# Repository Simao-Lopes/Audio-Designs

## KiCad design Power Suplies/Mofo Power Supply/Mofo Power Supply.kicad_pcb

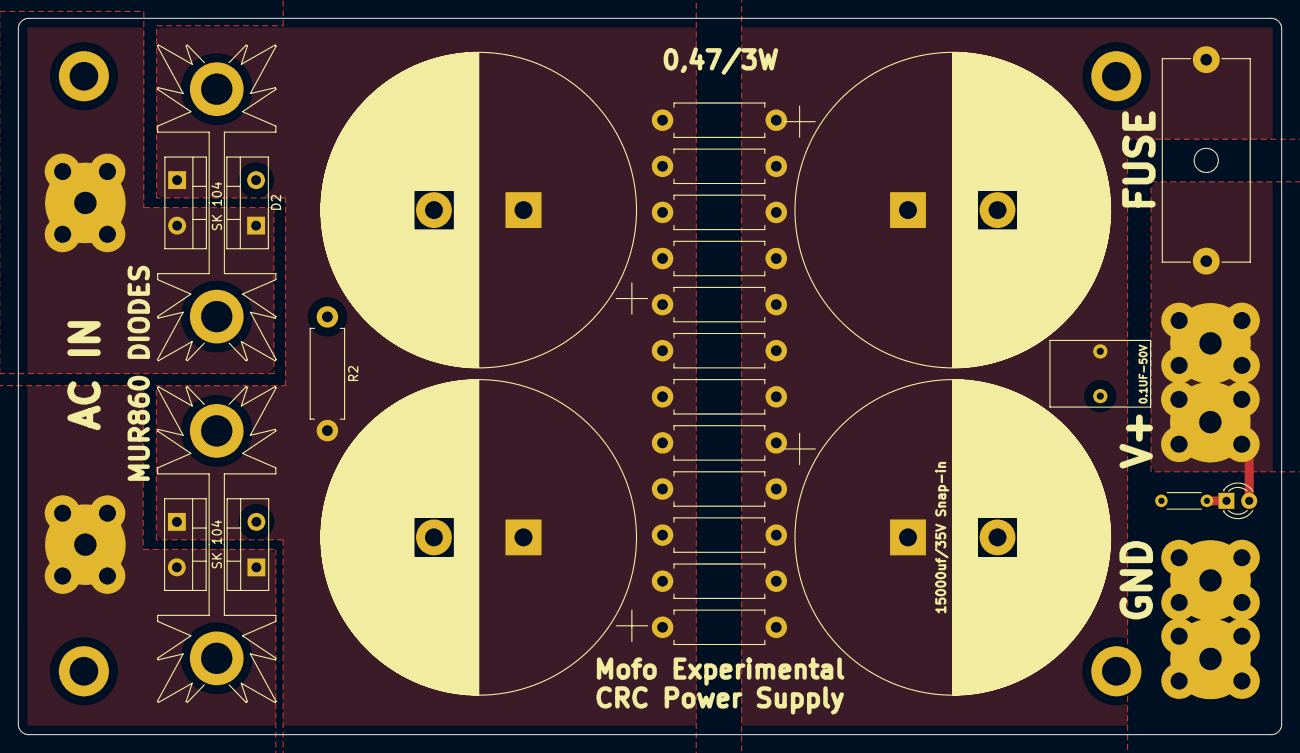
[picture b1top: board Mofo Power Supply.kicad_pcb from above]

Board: 2 copper layers, 141.1 x 80.0 mm, 35 parts (0 on the bottom side), 6 nets.

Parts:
0.1UF-50V: C; C_Rect_L7.2mm_W11.0mm_P5.00mm_FKS2_FKP2_MKS2_MKP2
AC1, AC2: Screw_Terminal_01x01; M4_Screw_Terminal
C1, C2, C3, C4: CP; CP_Radial_D35.0mm_P10.00mm_SnapIn
D1: LED; LED_D3.0mm
D2, D3, D4, D5: D; TO-220-2_Vertical
FUSE: Fuse; Fuseholder_Cylinder-5x20mm_Schurter_0031_8201_Horizontal_Op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
GND1, GND2: M4_Screw_Terminal
H1, H2, H3, H4: MountingHole; MountingHole_3.2mm_M3_DIN965_Pad
R2, R3, R3#2, R3#3, R4, R4#2, R4#3, R5, R5#2, R5#3: R; R_Axial_DIN0411_L9.9mm_D3.6mm_P12.70mm_Horizontal
R6, R6#2, R6#3: R7; R_Axial_DIN0411_L9.9mm_D3.6mm_P12.70mm_Horizontal
R11: R; R_Axial_DIN0204_L3.6mm_D1.6mm_P5.08mm_Horizontal
V1+1, V2+1: M4_Screw_Terminal

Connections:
/GND: 0.1UF-50V.2, C1.2, C2.2, C3.2, C4.2, D2.2 (A), D4.2 (A), GND1.1, GND2.1, R2.1, R11.1
/V+: 0.1UF-50V.1, C1.1, C2.1, C3.1, C4.1, D3.1 (K), D5.1 (K), FUSE.2, R2.2, R3.1, R3.2, R3#2.1, R3#2.2, R3#3.1, R3#3.2, R4.1, R4.2, R4#2.1, R4#2.2, R4#3.1, R4#3.2, R5.1, R5.2, R5#2.1, R5#2.2, R5#3.1, R5#3.2, R6.1, R6.2, R6#2.1, R6#2.2, R6#3.1, R6#3.2
unnamed: AC1.1, D4.1 (K), D5.2 (A)
unnamed: AC2.1, D2.1 (K), D3.2 (A)
unnamed: D1.1 (K), R11.2
unnamed: D1.2 (A), FUSE.1, V1+1.1, V2+1.1

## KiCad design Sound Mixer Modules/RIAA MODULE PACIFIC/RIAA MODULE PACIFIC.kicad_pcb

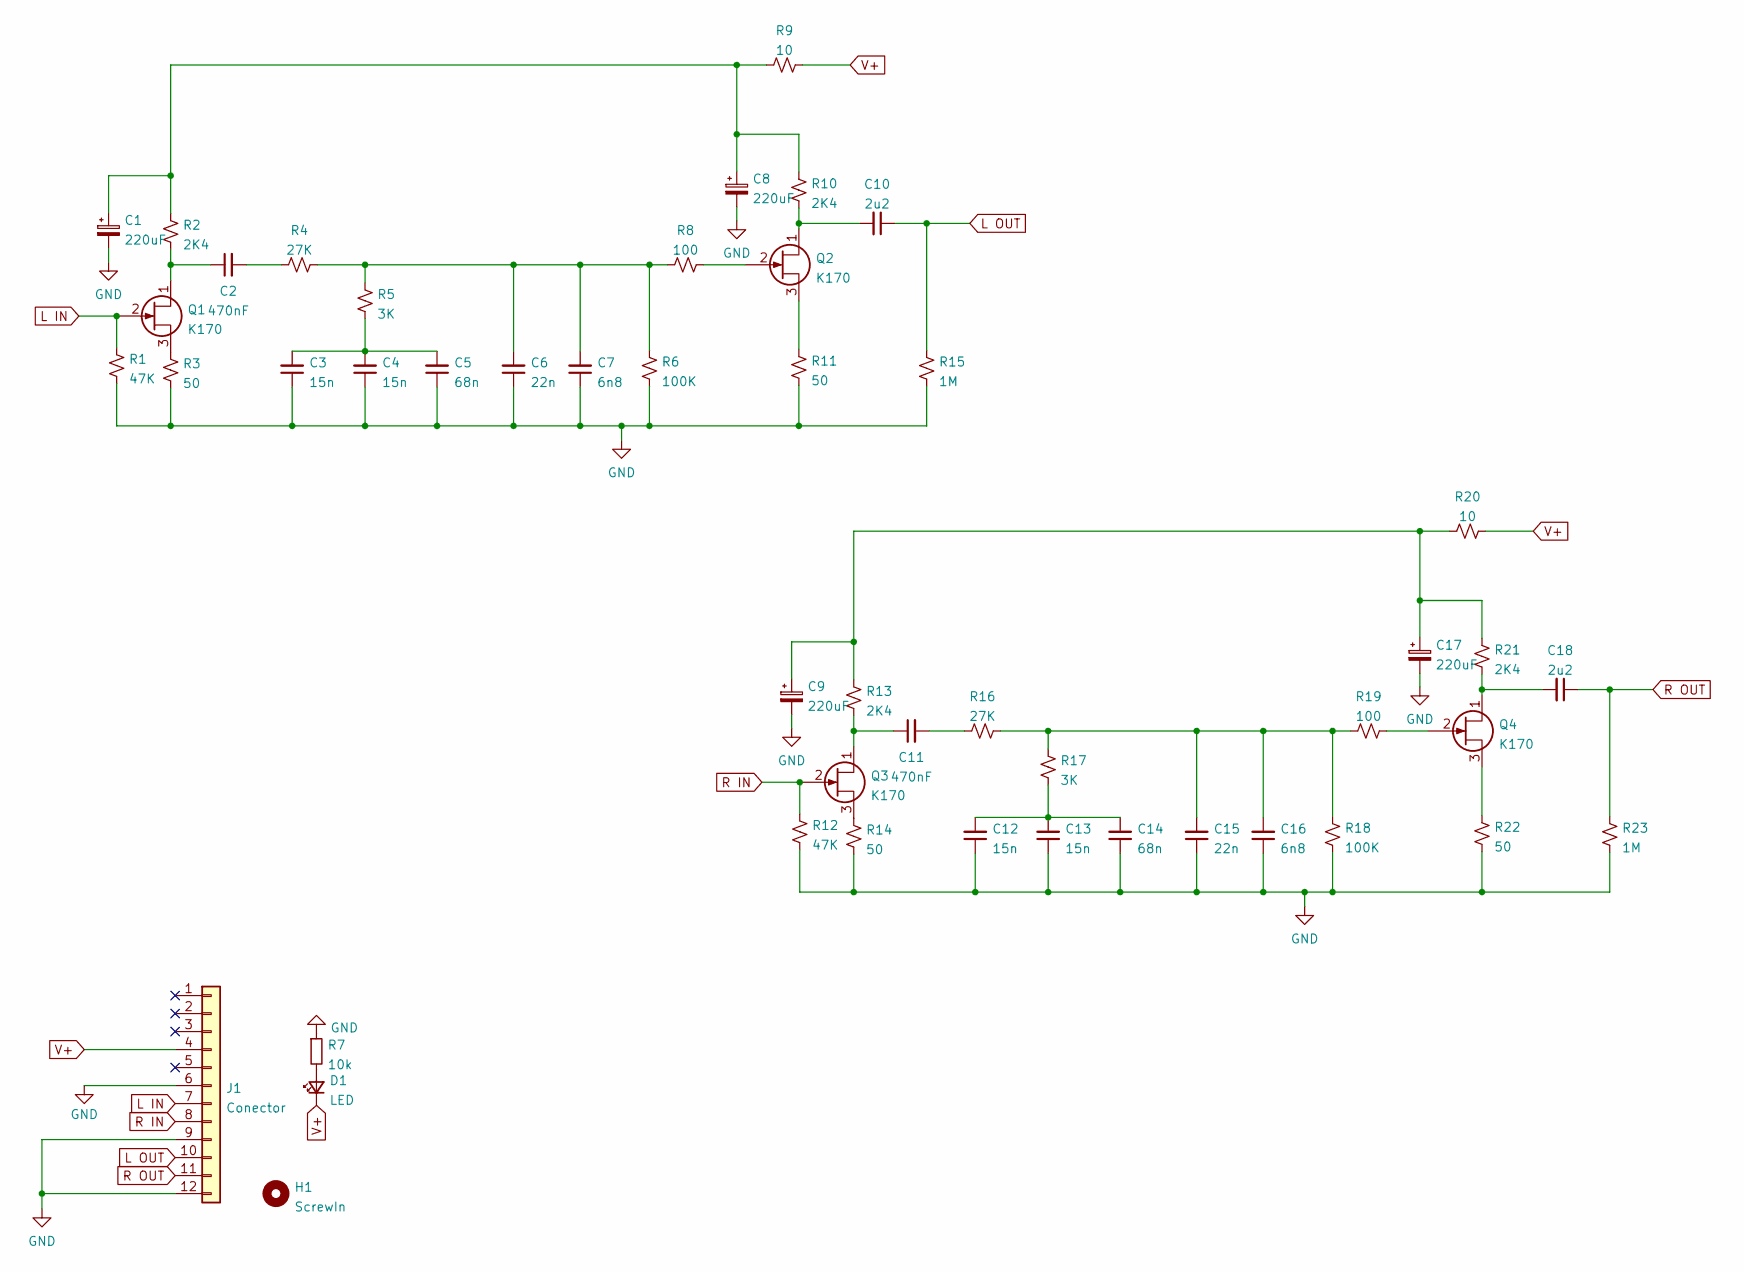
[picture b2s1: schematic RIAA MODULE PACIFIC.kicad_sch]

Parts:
C1, C8, C9, C17: 220uF; CP_Radial_D10.0mm_P5.00mm_P7.50mm
C2, C11: 470nF; C_Rect_L13.0mm_W8.0mm_P10.00mm_FKS3_FKP3_MKS4
C3, C4, C12, C13: 15n; C_Rect_L13.0mm_W8.0mm_P10.00mm_FKS3_FKP3_MKS4
C5, C14: 68n; C_Rect_L13.0mm_W8.0mm_P10.00mm_FKS3_FKP3_MKS4
C6, C15: 22n; C_Rect_L13.0mm_W8.0mm_P10.00mm_FKS3_FKP3_MKS4
C7, C16: 6n8; C_Rect_L13.0mm_W8.0mm_P10.00mm_FKS3_FKP3_MKS4
C10, C18: 2u2; C_Axial_L19.0mm_D8.0mm_P25.00mm_Horizontal
D1: LED; D_0201_0603Metric_Pad0.64x0.40mm_HandSolder
H1: ScrewIn; MountingHole_3.2mm_M3
J1: Conector; PinHeader_2x12_P2.54mm_Vertical
Q1, Q2, Q3, Q4: K170; TO-92
R1, R12: 47K; R_1206_3216Metric
R2, R10, R13, R21: 2K4; R_1206_3216Metric
R3, R11, R14, R22: 50; R_1206_3216Metric
R4, R16: 27K; R_1206_3216Metric
R5, R17: 3K; R_1206_3216Metric
R6, R18: 100K; R_1206_3216Metric
R7: 10k; R_1206_3216Metric
R8, R19: 100; R_1206_3216Metric
R9, R20: 10; R_1206_3216Metric
R15, R23: 1M; R_1206_3216Metric

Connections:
GND: C1.2, C3.1, C4.1, C5.1, C6.1, C7.1, C8.2, C9.2, C12.1, C13.1, C14.1, C15.1, C16.1, C17.2, J1.6, J1.9, J1.12, R1.2, R3.2, R6.1, R7.1, R11.2, R12.2, R14.2, R15.2, R18.1, R22.2, R23.2
L IN: J1.7, Q1.2 (G), R1.1
L OUT: C10.1, J1.10, R15.1
unnamed: C1.1, C8.1, R2.1, R9.1, R10.1
unnamed: C2.1, Q1.1 (D), R2.2
unnamed: C2.2, R4.1
unnamed: C3.2, C4.2, C5.2, R5.1
unnamed: C6.2, C7.2, R4.2, R5.2, R6.2, R8.2
unnamed: C10.2, Q2.1 (D), R10.2
unnamed: C11.1, Q3.1 (D), R13.2
unnamed: C11.2, R16.1
unnamed: C12.2, C13.2, C14.2, R17.1
unnamed: C15.2, C16.2, R16.2, R17.2, R18.2, R19.2
unnamed: C9.1, C17.1, R13.1, R20.1, R21.1
unnamed: C18.2, Q4.1 (D), R21.2
unnamed: D1.2 (A), R7.2
unnamed: Q1.3 (S), R3.1
unnamed: Q2.2 (G), R8.1
unnamed: Q2.3 (S), R11.1
unnamed: Q3.3 (S), R14.1
unnamed: Q4.2 (G), R19.1
unnamed: Q4.3 (S), R22.1
R IN: J1.8, Q3.2 (G), R12.1
R OUT: C18.1, J1.11, R23.1
V+: D1.1 (K), J1.4, R9.2, R20.2

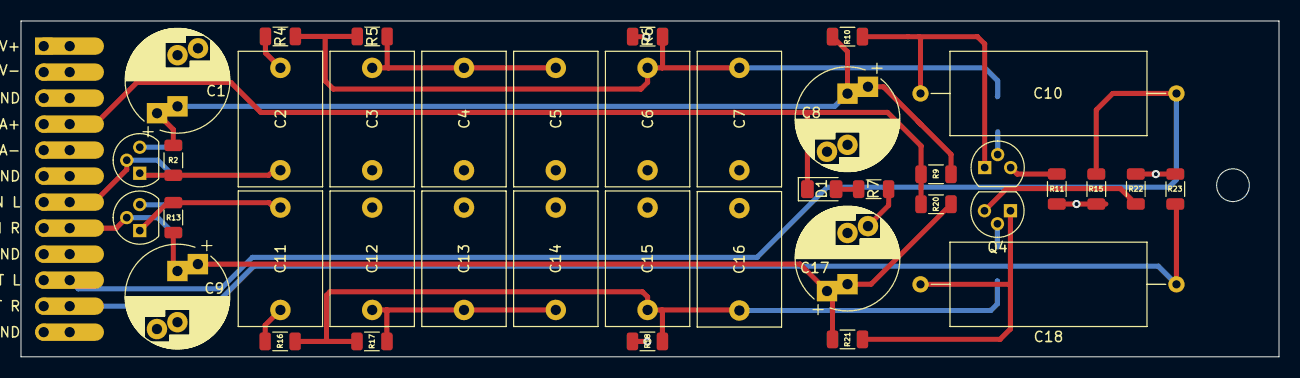
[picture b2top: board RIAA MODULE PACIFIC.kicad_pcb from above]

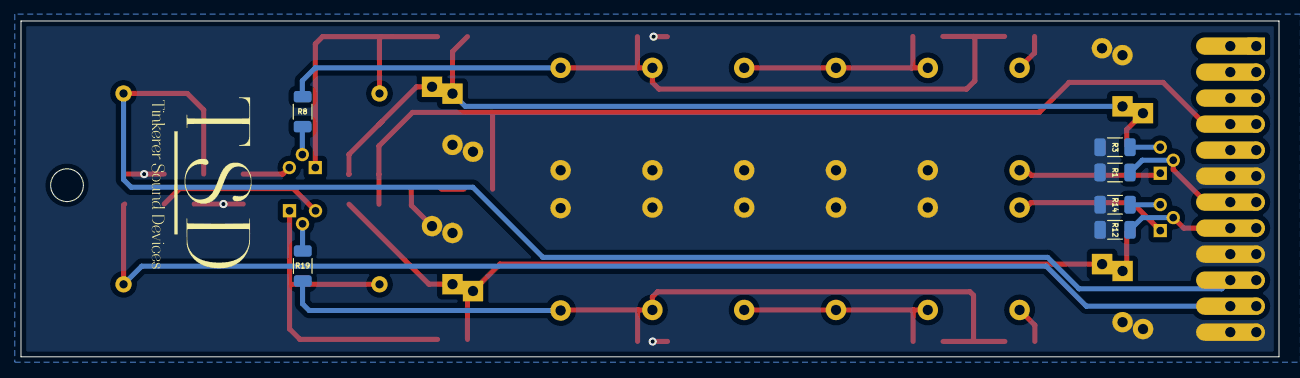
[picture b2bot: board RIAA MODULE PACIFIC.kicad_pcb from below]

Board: 2 copper layers, 122.9 x 32.8 mm, 48 parts (6 on the bottom side), 25 nets.

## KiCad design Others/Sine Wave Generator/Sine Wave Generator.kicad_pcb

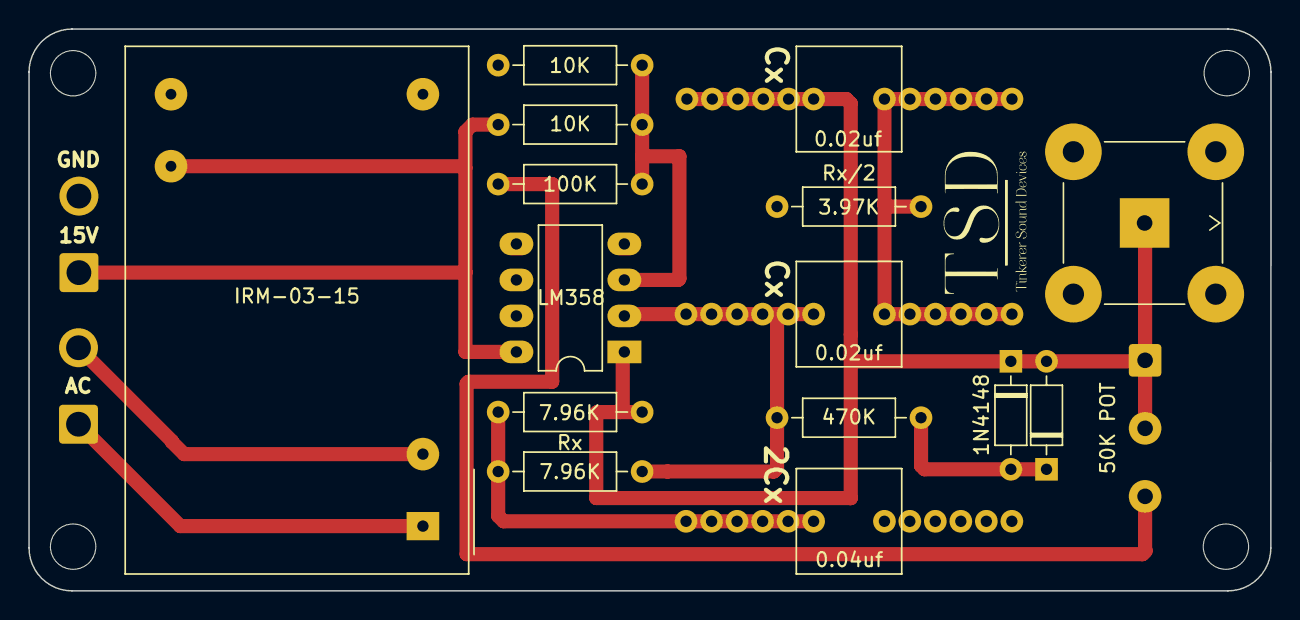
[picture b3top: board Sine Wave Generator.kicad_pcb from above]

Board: 2 copper layers, 87.6 x 39.7 mm, 21 parts (0 on the bottom side), 11 nets.

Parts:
1, 2, 3: (no value)
15V: AC; SolderWire-1sqmm_1x02_P5.4mm_D1.4mm_OD2.7mm
50K POT: 50K; SolderWire-0.5sqmm_1x03_P4.8mm_D0.9mm_OD2.3mm
AC: AC; SolderWire-1sqmm_1x02_P5.4mm_D1.4mm_OD2.7mm
C3, C5: 0.02uf; C_Rect_L7.2mm_W7.2mm_P5.00mm_FKS2_FKP2_MKS2_MKP2
C4: 0.04uf; C_Rect_L7.2mm_W7.2mm_P5.00mm_FKS2_FKP2_MKS2_MKP2
D1, D2: 1N4148; D_DO-35_SOD27_P7.62mm_Horizontal
J3: Conn_Coaxial; BNC_TEConnectivity_1478035_Horizontal
PS1: IRM-03-15; Converter_ACDC_MeanWell_IRM-03-xx_THT
R1, R2: 10K; R_Axial_DIN0207_L6.3mm_D2.5mm_P10.16mm_Horizontal
R4: 100K; R_Axial_DIN0207_L6.3mm_D2.5mm_P10.16mm_Horizontal
R5: 470K; R_Axial_DIN0207_L6.3mm_D2.5mm_P10.16mm_Horizontal
R7: 7.96K; R_Axial_DIN0207_L6.3mm_D2.5mm_P10.16mm_Horizontal
Rx: 7.96K; R_Axial_DIN0207_L6.3mm_D2.5mm_P10.16mm_Horizontal
Rx/2: 3.97K; R_Axial_DIN0207_L6.3mm_D2.5mm_P10.16mm_Horizontal
U1: LM358; DIP-8_W7.62mm_LongPads

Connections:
GND: 15V.2, C4.1, J3.2 (Ext), PS1.14 (-Vo), R2.2, Rx/2.1, U1.4 (V-)
unnamed: C3.1, R5.1, Rx.1, U1.2 (-)
unnamed: C3.2, C5.1, Rx/2.2
unnamed: C4.2, R7.1, Rx.2
unnamed: 1.2, 2.2, 3.2, 50K POT.1, 50K POT.2, C5.2, D1.1 (K), D2.2 (A), J3.1 (In), R7.2, U1.1
unnamed: D1.2 (A), D2.1 (K), R5.2
unnamed: AC.1, PS1.1 (AC/L)
unnamed: AC.2, PS1.3 (AC/N)
unnamed: 15V.1, PS1.16 (+Vo), R1.1, U1.8 (V+)
unnamed: R1.2, R2.1, R4.1, U1.3 (+)
unnamed: 50K POT.3, R4.2

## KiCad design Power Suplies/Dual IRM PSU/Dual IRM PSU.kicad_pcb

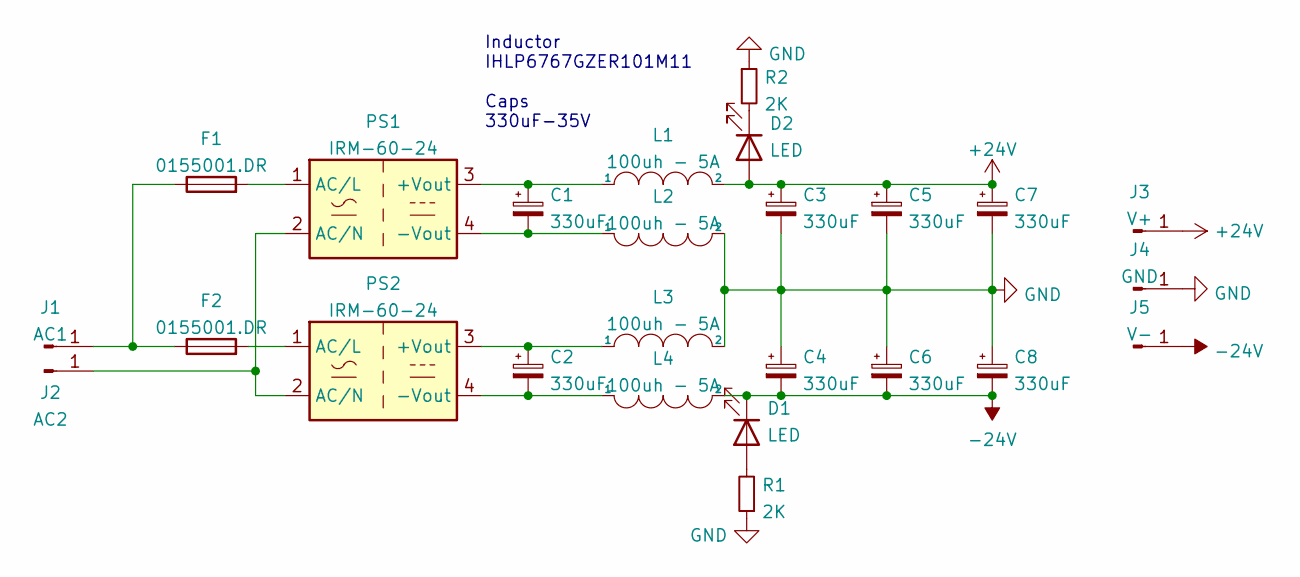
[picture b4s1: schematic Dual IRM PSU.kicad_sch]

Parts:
C1, C2, C3, C4, C5, C6, C7, C8: 330uF; CP_Elec_16x17.5
D1, D2: LED; LED_1210_3225Metric
F1, F2: 0155001.DR; Fuseholder_Littelfuse_100_series_5x20mm
J1: AC1; Spade Conector 6.3mm TE_1217861
J2: AC2; Spade Conector 6.3mm TE_1217861
J3: V+; Spade Conector 6.3mm TE_1217861
J4: GND; Spade Conector 6.3mm TE_1217861
J5: V-; Spade Conector 6.3mm TE_1217861
L1, L2, L3, L4: 100uh - 5A; L_Vishay_IHLP-6767
PS1, PS2: IRM-60-24; Converter_ACDC_MeanWell_IRM-60-xx_THT
R1, R2: 2K; R_1210_3225Metric

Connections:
+24V: C3.1, C5.1, C7.1, D2.2 (A), J3.1, L1.2
-24V: C4.2, C6.2, C8.2, D1.1 (K), J5.1, L4.2
GND: C3.2, C4.1, C5.2, C6.1, C7.2, C8.1, J4.1, L2.2, L3.2, R1.1, R2.1
unnamed: C1.1, L1.1, PS1.3 (+Vout)
unnamed: C1.2, L2.1, PS1.4 (-Vout)
unnamed: C2.1, L3.1, PS2.3 (+Vout)
unnamed: C2.2, L4.1, PS2.4 (-Vout)
unnamed: D1.2 (A), R1.2
unnamed: D2.1 (K), R2.2
unnamed: F1.1, F2.1, J1.1
unnamed: F1.2, PS1.1 (AC/L)
unnamed: F2.2, PS2.1 (AC/L)
unnamed: J2.1, PS1.2 (AC/N), PS2.2 (AC/N)

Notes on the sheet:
Inductor IHLP6767GZER101M11 Caps 330uF-35V

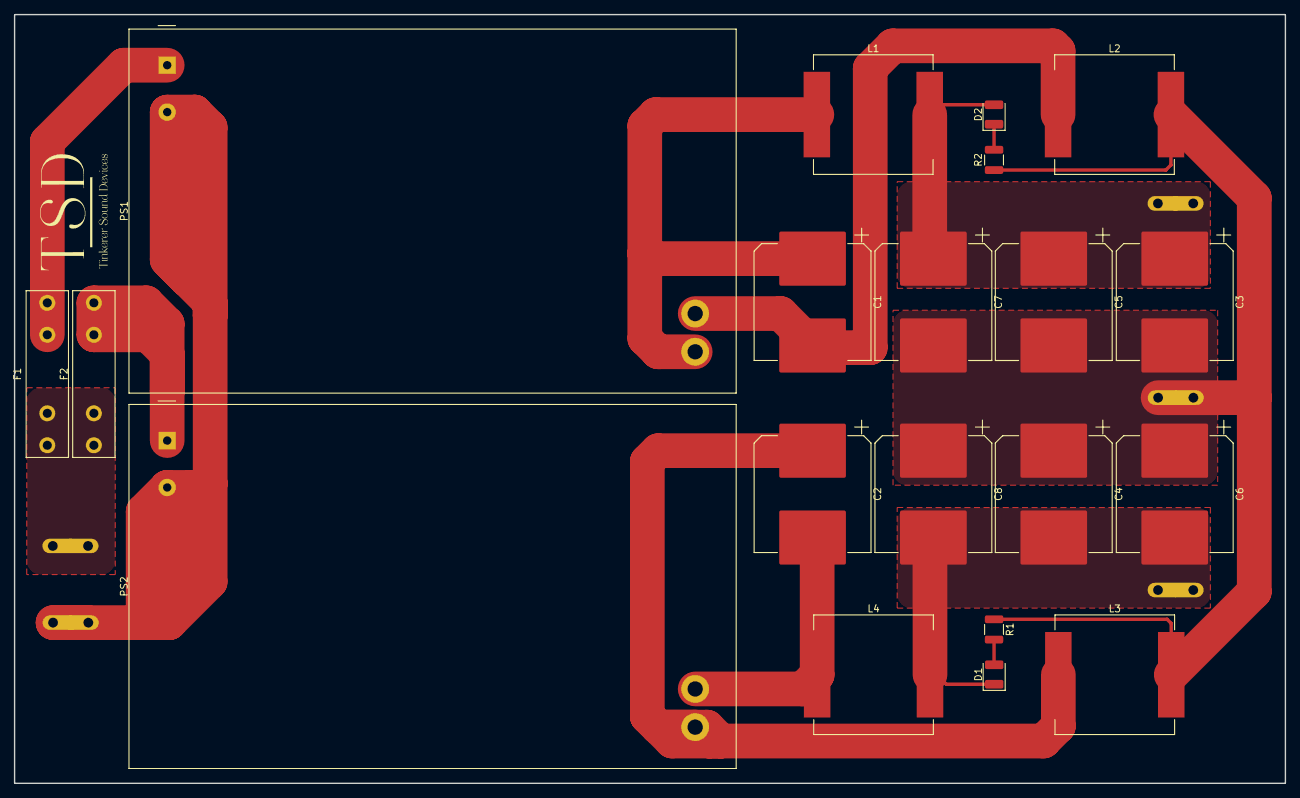
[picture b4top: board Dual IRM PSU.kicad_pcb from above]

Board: 2 copper layers, 182.9 x 110.7 mm, 25 parts (0 on the bottom side), 13 nets.

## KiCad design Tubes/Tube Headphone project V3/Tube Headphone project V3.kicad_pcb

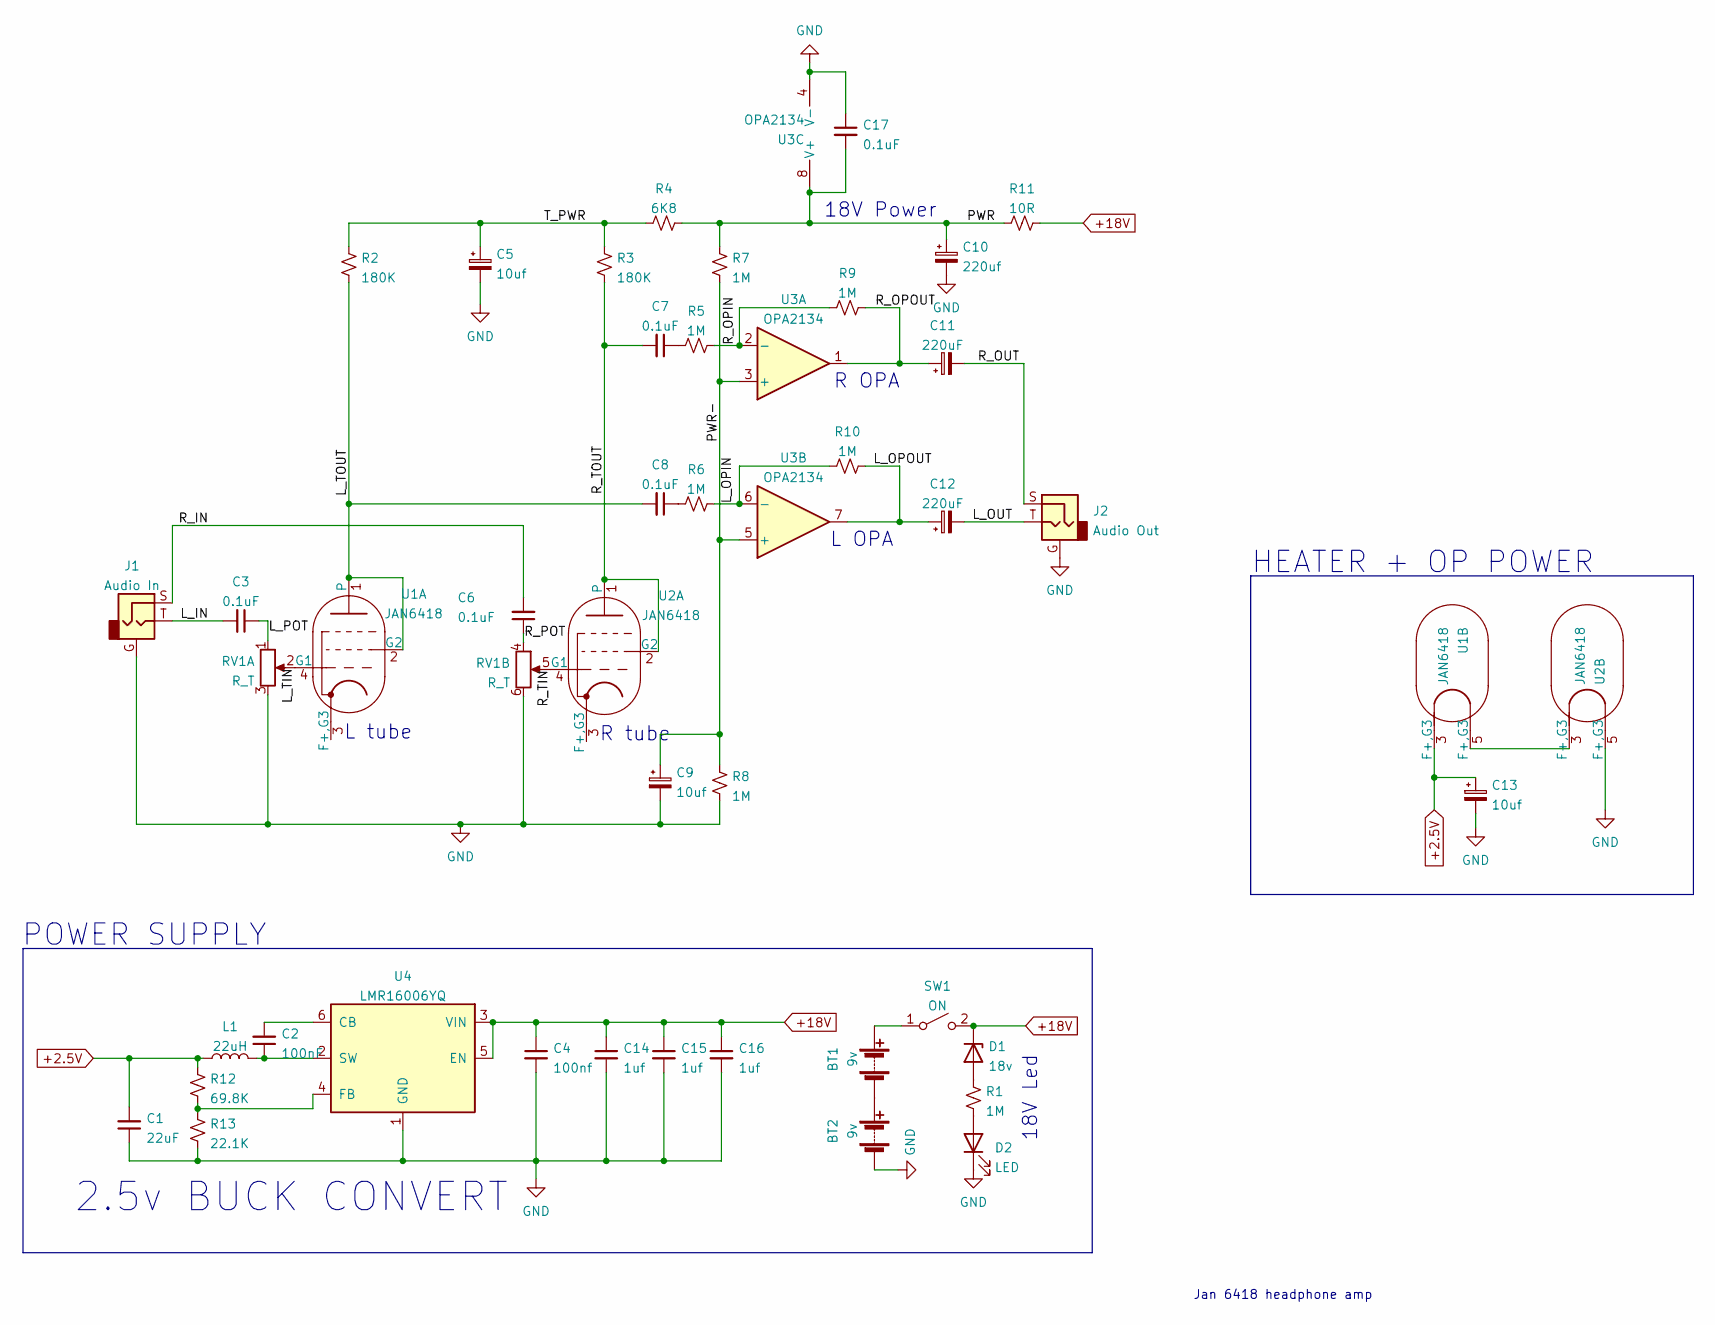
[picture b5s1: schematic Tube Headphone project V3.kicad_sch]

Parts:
BT1, BT2: 9v; BatteryHolder_Eagle_12BH611-GR
C1: 22uF; C_0603_1608Metric_Pad1.08x0.95mm_HandSolder
C2: 100nF; C_0402_1005Metric_Pad0.74x0.62mm_HandSolder
C3, C6, C7, C8: 0.1uF; C_Rect_L7.2mm_W7.2mm_P5.00mm_FKS2_FKP2_MKS2_MKP2
C4: 100nf; C_0603_1608Metric_Pad1.08x0.95mm_HandSolder
C5, C9, C13: 10uf; CP_Radial_D5.0mm_P2.50mm
C10: 220uf; CP_Radial_D10.0mm_P5.00mm_P7.50mm
C11, C12: 220uF; CP_Radial_D10.0mm_P5.00mm_P7.50mm
C14, C15, C16: 1uf; C_0603_1608Metric_Pad1.08x0.95mm_HandSolder
C17: 0.1uF; C_Rect_L7.2mm_W3.5mm_P5.00mm_FKS2_FKP2_MKS2_MKP2
D1: 18v; D_1206_3216Metric_Pad1.42x1.75mm_HandSolder
D2: LED; LED_1206_3216Metric_Pad1.42x1.75mm_HandSolder
J1: Audio In; ACJSMHD985
J2: Audio Out; ACJSMHD985
L1: 22uH; L_Bourns_SDR1806
R1, R5, R6, R7, R8, R9, R10: 1M; R_1206_3216Metric_Pad1.30x1.75mm_HandSolder
R2, R3: 180K; R_1206_3216Metric_Pad1.30x1.75mm_HandSolder
R4: 6K8; R_1206_3216Metric_Pad1.30x1.75mm_HandSolder
R11: 10R; R_1206_3216Metric_Pad1.30x1.75mm_HandSolder
R12: 69.8K; R_0402_1005Metric_Pad0.72x0.64mm_HandSolder
R13: 22.1K; R_0402_1005Metric_Pad0.72x0.64mm_HandSolder
RV1: R_T; Potentiometer_Alps_RK097_Dual_Horizontal
SW1: ON; JST_EH_B2B-EH-A_1x02_P2.50mm_Vertical
U1, U2: JAN6418; Valve_Mini_Pentode_Linear
U3: OPA2134; DIP-8_W7.62mm
U4: LMR16006YQ; SOT-23-6

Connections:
+2.5V: C1.2, C13.1, L1.1, R12.1, U1.3 (F+,G3)
+18V: C4.1, C14.1, C15.1, C16.1, D1.1 (K), R11.1, SW1.2 (B), U4.3 (VIN), U4.5 (EN); also elsewhere on the board
/L_IN: C3.2, J1.T
/L_OPIN: R6.2, R10.1, U3.6 (-)
/L_OPOUT: C12.1, R10.2, U3.7
/L_OUT: C12.2, J2.T
/L_POT: C3.1, RV1.1
/L_TIN: RV1.2, U1.4 (G1)
/L_TOUT: C8.2, R2.1, U1.1, U1.2 (G2)
/PWR: C10.1, C17.2, R4.1, R7.2, R11.2, U3.8 (V+)
/PWR-: C9.1, R7.1, R8.1, U3.3 (+), U3.5 (+)
/R_IN: C6.2, J1.S
/R_OPIN: R5.2, R9.1, U3.2 (-)
/R_OPOUT: C11.1, R9.2, U3.1
/R_OUT: C11.2, J2.S
/R_POT: C6.1, RV1.4
/R_TIN: RV1.5, U2.4 (G1)
/R_TOUT: C7.2, R3.1, U2.1, U2.2 (G2)
/T_PWR: C5.1, R2.2, R3.2, R4.2
GND: BT2.2 (-), C1.1, C4.2, C5.2, C9.2, C10.2, C13.2, C14.2, C15.2, C16.2, C17.1, D2.1 (K), J1.G, J2.G, R8.2, R13.2, RV1.3, RV1.6, U2.5 (F+,G3), U3.4 (V-), U4.1 (GND)
unnamed 20: BT1.1 (+), SW1.1 (A); also elsewhere on the board
unnamed: BT1.2 (-), BT2.1 (+)
unnamed: C2.1, L1.2, U4.2 (SW)
unnamed: C2.2, U4.6 (CB)
unnamed: C7.1, R5.1
unnamed: C8.1, R6.1
unnamed: D1.2 (A), R1.2
unnamed: D2.2 (A), R1.1
unnamed: R12.2, R13.1, U4.4 (FB)
unnamed: U1.5 (F+,G3), U2.3 (F+,G3)

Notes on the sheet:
18V Led
POWER SUPPLY
L tube
R OPA
2.5v BUCK CONVERT
R tube
Jan 6418 headphone amp
L OPA
HEATER + OP POWER
18V Power

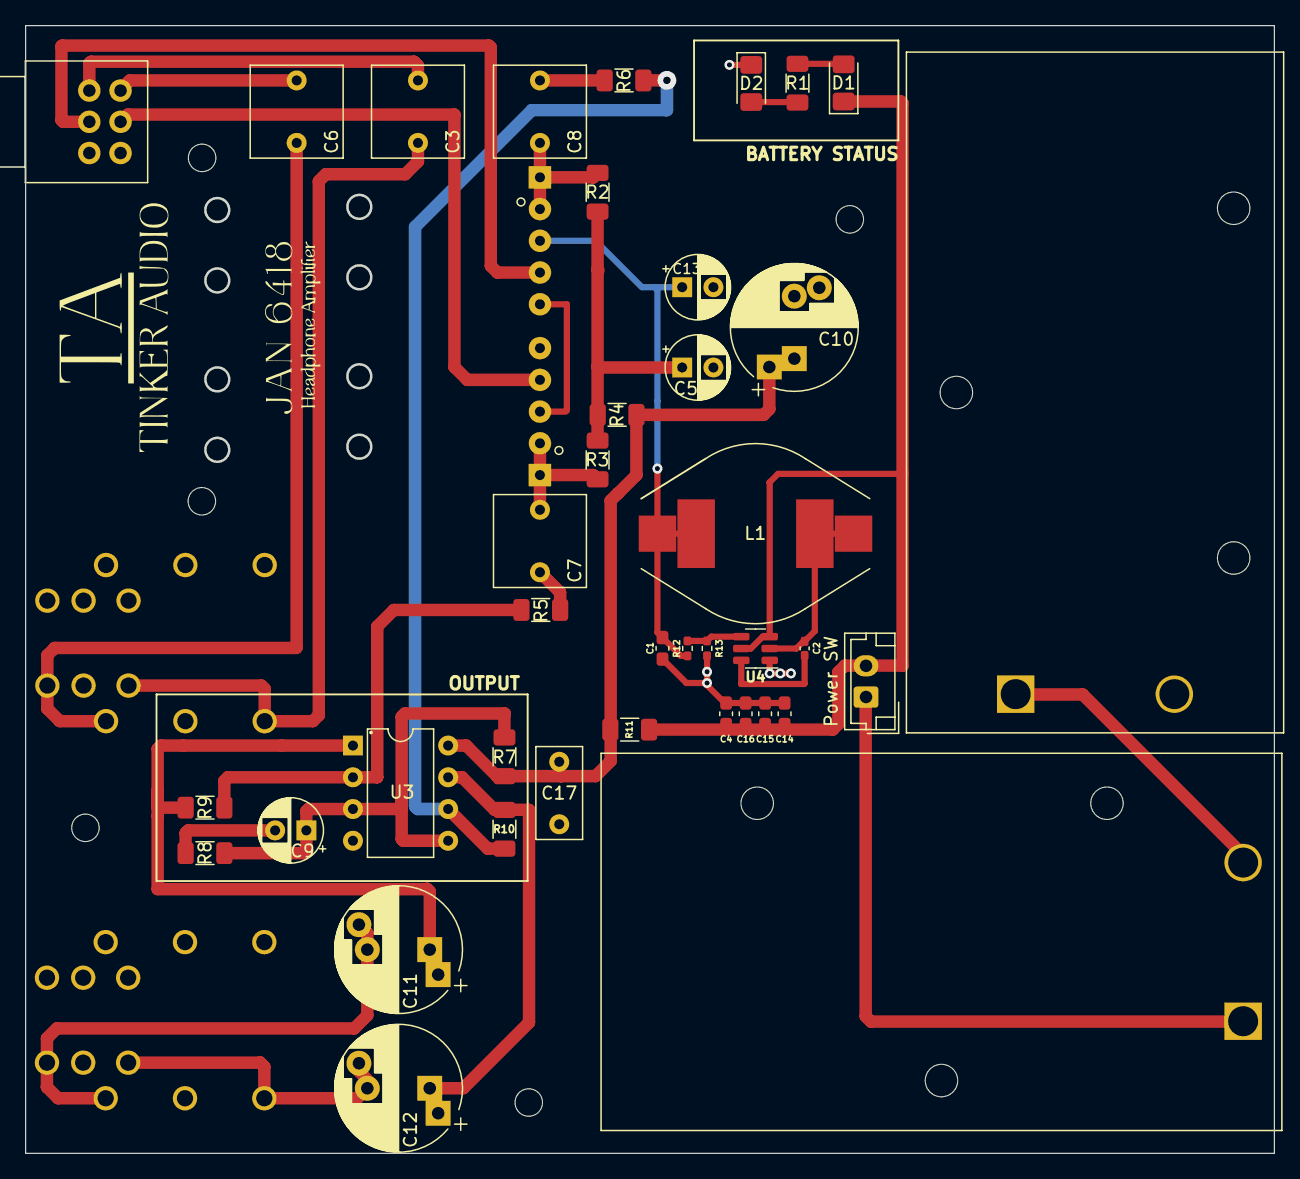
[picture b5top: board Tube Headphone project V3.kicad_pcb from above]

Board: 2 copper layers, 100.0 x 90.3 mm, 43 parts (0 on the bottom side), 30 nets.

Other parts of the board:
Power SW: ON; JST_EH_B2B-EH-A_1x02_P2.50mm_Vertical

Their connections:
+18V: Power SW.2 (B); also elsewhere on the board
unnamed 20: Power SW.1 (A); also elsewhere on the board

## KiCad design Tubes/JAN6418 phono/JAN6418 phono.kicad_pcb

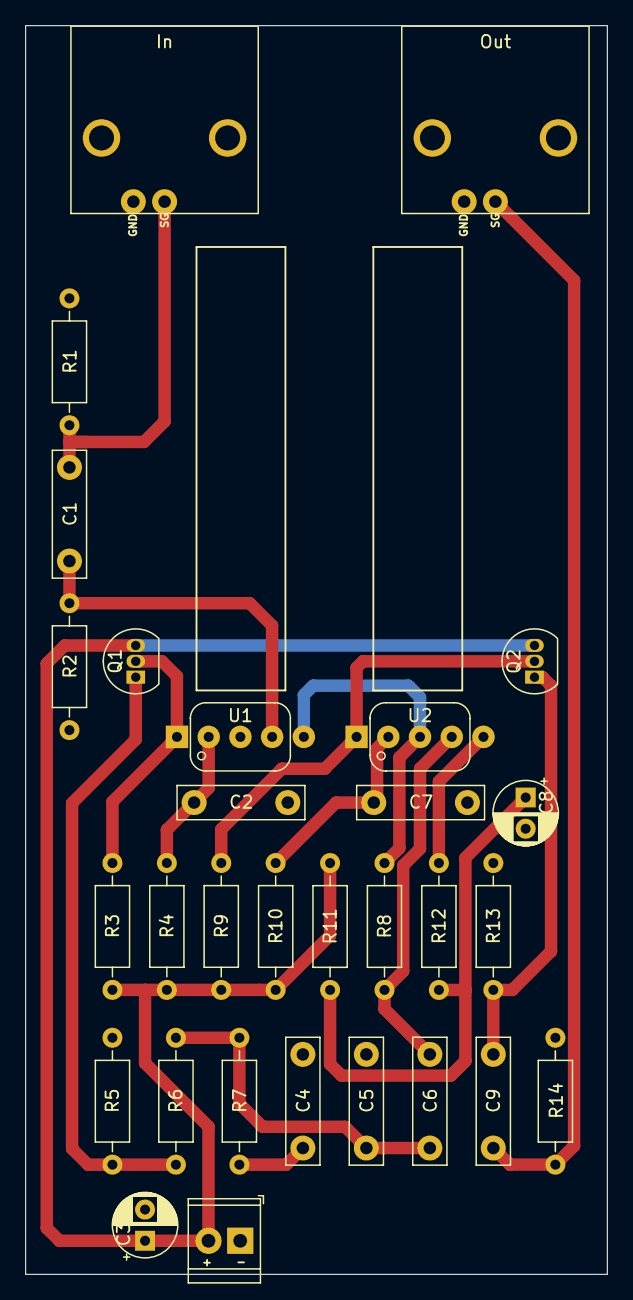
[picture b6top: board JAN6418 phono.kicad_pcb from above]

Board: 2 copper layers, 46.6 x 100.0 mm, 30 parts (0 on the bottom side), 17 nets.

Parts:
C1, C2, C6, C7: 0.1uF; C_Rect_L10.0mm_W2.5mm_P7.50mm_MKS4
C3, C8: 4.7uF; CP_Radial_D5.0mm_P2.50mm
C4: 6n8; C_Rect_L10.0mm_W2.5mm_P7.50mm_MKS4
C5: 0.022uf; C_Rect_L10.0mm_W2.5mm_P7.50mm_MKS4
C9: 0.39uF; C_Rect_L10.0mm_W2.5mm_P7.50mm_MKS4
In: In; RCA PANEL 2PIN FOOTPRINT
J3: Power; TerminalBlock_TE_282834-2_1x02_P2.54mm_Horizontal
Out: Out; RCA PANEL 2PIN FOOTPRINT
Q1, Q2: BSN254A; TO-92_Inline
R1, R3, R9: 100K; R_Axial_DIN0207_L6.3mm_D2.5mm_P10.16mm_Horizontal
R2, R14: 1M; R_Axial_DIN0207_L6.3mm_D2.5mm_P10.16mm_Horizontal
R4, R10: 330K; R_Axial_DIN0207_L6.3mm_D2.5mm_P10.16mm_Horizontal
R5, R7, R8, R13: 10K; R_Axial_DIN0207_L6.3mm_D2.5mm_P10.16mm_Horizontal
R6: 82K; R_Axial_DIN0207_L6.3mm_D2.5mm_P10.16mm_Horizontal
R11: 1.5K; R_Axial_DIN0207_L6.3mm_D2.5mm_P10.16mm_Horizontal
R12: 1.2K; R_Axial_DIN0207_L6.3mm_D2.5mm_P10.16mm_Horizontal
U1, U2: JAN6418; Valve_Mini_Pentode_Linear

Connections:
1: U1.5 (F+,G3), U2.3 (F+,G3)
+30V: C3.1, J3.2, Q1.3 (S), Q2.3 (S), R3.1, R4.1, R9.1, R10.1, R11.1
GND: C2.1, C3.2, C4.1, C5.1, C7.1, C8.2, In.2, J3.1, Out.2, R1.2, R2.2, R5.2, R13.2, R14.2, U1.3 (F+,G3)
In: C1.1, In.1, R1.1
unnamed: C1.2, R2.1, U1.4 (G1)
unnamed: C2.2, R4.2, U1.2 (G2)
unnamed: C4.2, R7.2
unnamed: C5.2, C6.2, R6.2, R7.1
unnamed: C6.1, R8.1, U2.4 (G1)
unnamed: C7.2, R10.2, U2.2 (G2)
unnamed: C8.1, R11.2, R12.1
unnamed: C9.2, Q2.1 (D), R13.1
unnamed: Q1.1 (D), R5.1, R6.1
unnamed: Q1.2 (G), R3.2, U1.1
unnamed: Q2.2 (G), R9.2, U2.1
Out: C9.1, Out.1, R14.1
heater: R12.2, U2.5 (F+,G3)

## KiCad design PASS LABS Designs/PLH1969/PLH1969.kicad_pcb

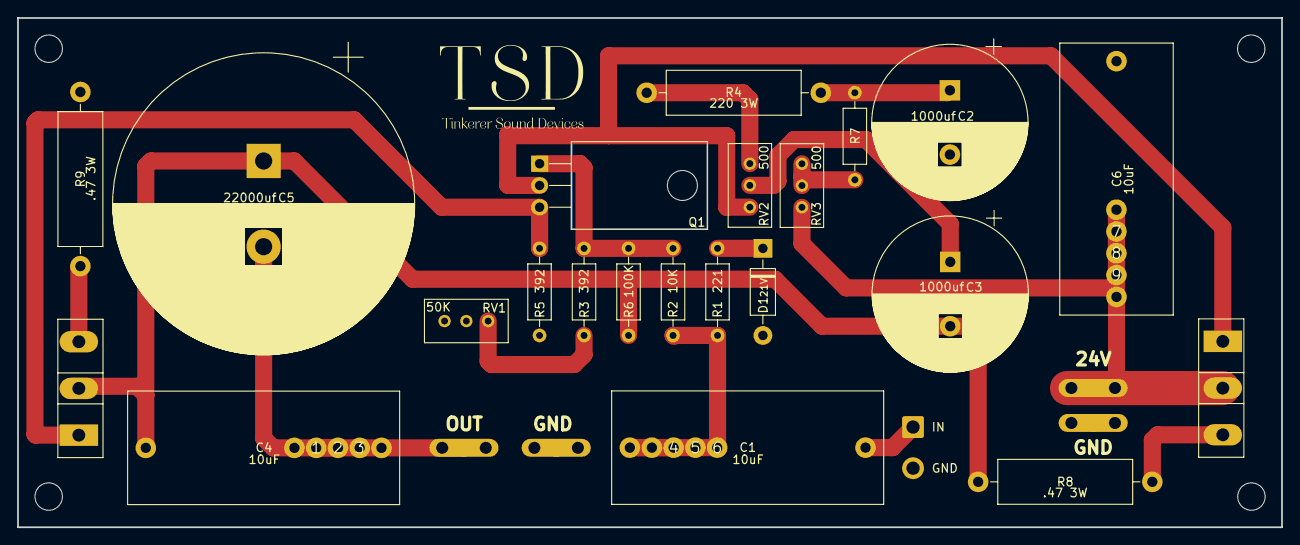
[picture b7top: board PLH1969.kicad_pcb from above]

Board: 2 copper layers, 147.5 x 59.4 mm, 36 parts (0 on the bottom side), 17 nets.

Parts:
1, 2, 3, 4, 5, 6, 7, 8, 9: (no value)
C1, C4, C6: 10uF; C_Rect_L31.5mm_W13.0mm_P27.50mm_MKS4
C2, C3: 1000uf; CP_Radial_D18.0mm_P7.50mm
C5: 22000uf; CP_Radial_D35.0mm_P10.00mm_SnapIn
D1: 21V; D_DO-41_SOD81_P10.16mm_Horizontal
IN: IN; SolderWire-0.75sqmm_1x02_P4.8mm_D1.25mm_OD2.3mm
J2: 40V; Spade Conector 6.3mm TE_1217861
J3: OUT; Spade Conector 6.3mm TE_1217861
J5, J5#2: GND; Spade Conector 6.3mm TE_1217861
Q1: IRF610; TO-220-3_Horizontal_TabDown
Q2, Q3: IRF244; TO-247-3_Vertical
R1, R7: 221; R_Axial_DIN0207_L6.3mm_D2.5mm_P10.16mm_Horizontal
R2: 10K; R_Axial_DIN0207_L6.3mm_D2.5mm_P10.16mm_Horizontal
R3, R5: 392; R_Axial_DIN0207_L6.3mm_D2.5mm_P10.16mm_Horizontal
R4: 220 3W; R_Axial_DIN0516_L15.5mm_D5.0mm_P20.32mm_Horizontal
R6: 100K; R_Axial_DIN0207_L6.3mm_D2.5mm_P10.16mm_Horizontal
R8, R9: .47 3W; R_Axial_DIN0516_L15.5mm_D5.0mm_P20.32mm_Horizontal
RV1: 50K; Potentiometer_Bourns_3296W_Vertical
RV2, RV3: 500; Potentiometer_Bourns_3296W_Vertical

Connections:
GND: C2.2, C6.1, D1.2 (A), IN.2, J5.1, J5#2.1, R5.2, R9.2, RV1.1, RV1.2
unnamed: C1.1, IN.1
unnamed: 4.2, 5.2, 6.2, C1.2, R1.1, R2.1
unnamed: C2.1, R4.1, R7.1
unnamed: C3.1, RV2.2
unnamed: C3.2, C4.1, C5.1, Q3.2 (D), R6.2, R8.2
unnamed: 1.2, 2.2, 3.2, C4.2, C5.2, J3.1
unnamed: 7.2, 8.2, 9.2, C6.2, J2.1, Q2.2 (D), RV3.1
unnamed: D1.1 (K), R1.2
unnamed: Q1.1 (G), R2.2, R3.1, R6.1
unnamed: Q1.2 (D), Q2.1 (G), RV2.3
unnamed: Q1.3 (S), Q3.1 (G), R5.1
unnamed: Q2.3 (S), R8.1
unnamed: Q3.3 (S), R9.1
unnamed: R3.2, RV1.3
unnamed: R4.2, RV2.1
unnamed: R7.2, RV3.2, RV3.3

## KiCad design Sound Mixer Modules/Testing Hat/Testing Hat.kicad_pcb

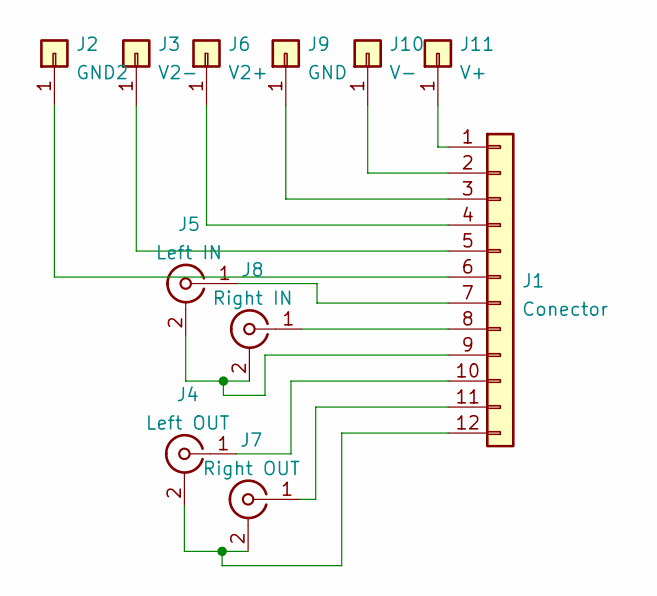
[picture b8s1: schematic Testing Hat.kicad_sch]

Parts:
J1: Conector; PinSocket_2x12_P2.54mm_Vertical
J2: GND2; Spade Conector 6.3mm TE_1217861
J3: V2-; Spade Conector 6.3mm TE_1217861
J4: Left OUT; RCA PANEL 2PIN FOOTPRINT
J5: Left IN; RCA PANEL 2PIN FOOTPRINT
J6: V2+; Spade Conector 6.3mm TE_1217861
J7: Right OUT; RCA PANEL 2PIN FOOTPRINT
J8: Right IN; RCA PANEL 2PIN FOOTPRINT
J9: GND; Spade Conector 6.3mm TE_1217861
J10: V-; Spade Conector 6.3mm TE_1217861
J11: V+; Spade Conector 6.3mm TE_1217861

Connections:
unnamed: J1.1, J11.1
unnamed: J1.2, J10.1
unnamed: J1.3, J9.1
unnamed: J1.4, J6.1
unnamed: J1.5, J3.1
unnamed: J1.6, J2.1
unnamed: J1.7, J5.1 (In)
unnamed: J1.8, J8.1 (In)
unnamed: J1.9, J5.2 (Ext), J8.2 (Ext)
unnamed: J1.10, J4.1 (In)
unnamed: J1.11, J7.1 (In)
unnamed: J1.12, J4.2 (Ext), J7.2 (Ext)

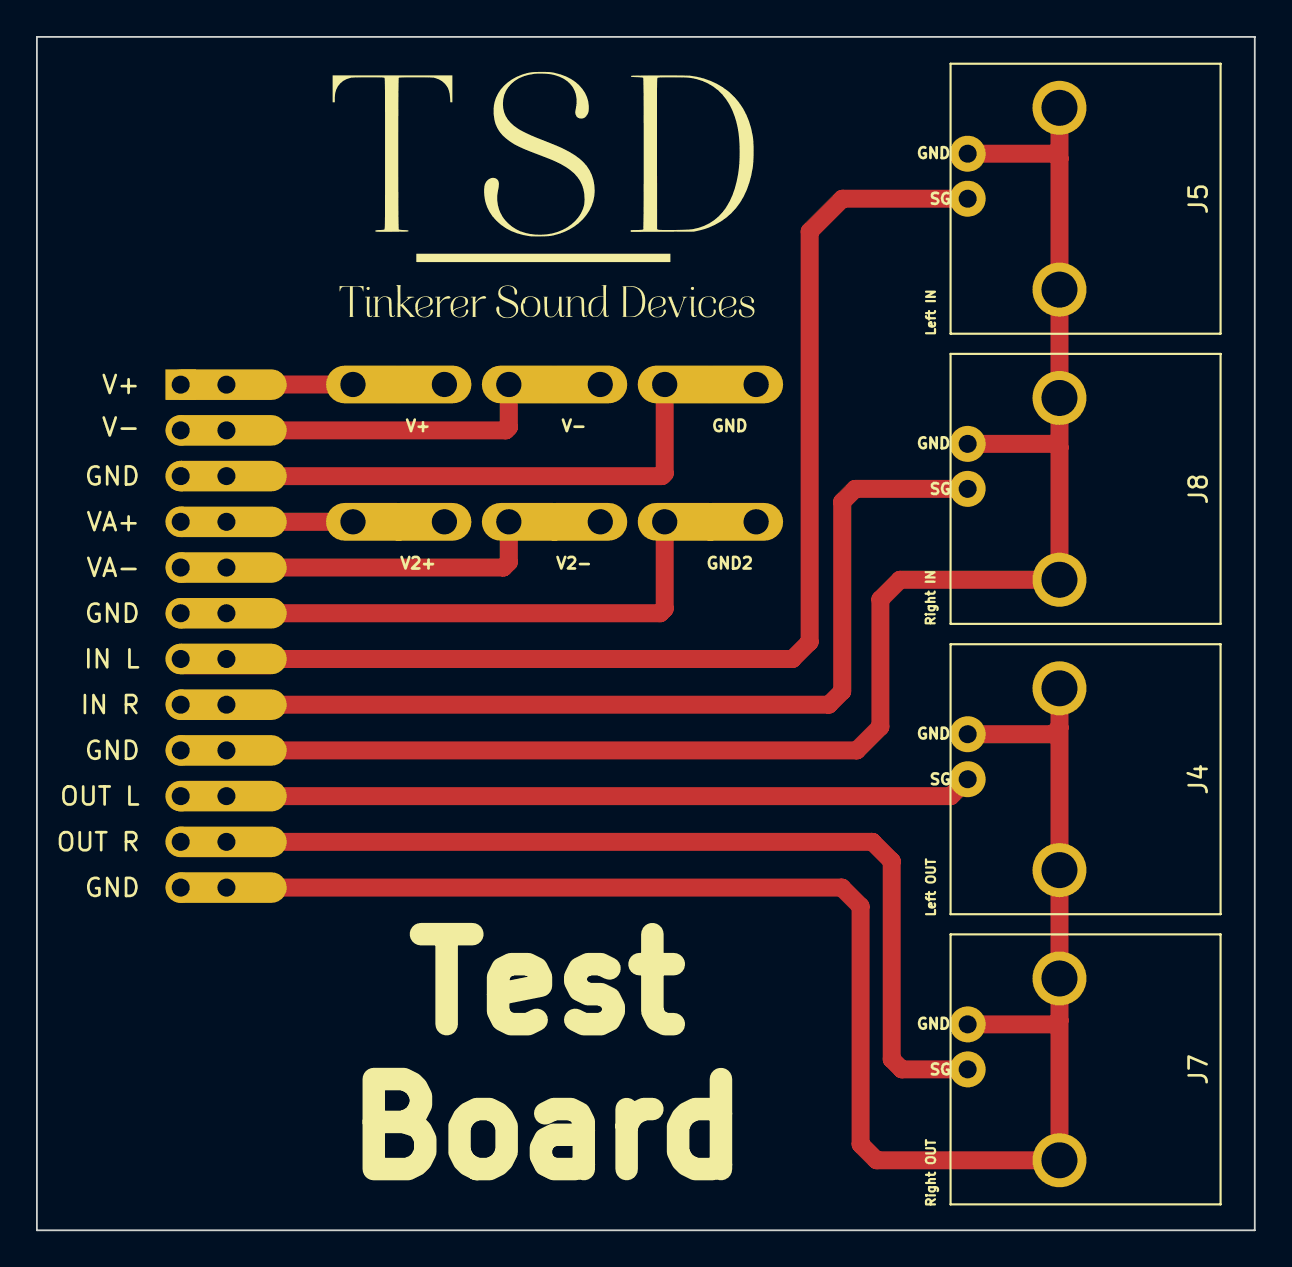
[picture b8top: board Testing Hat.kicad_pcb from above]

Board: 2 copper layers, 67.7 x 66.3 mm, 11 parts (0 on the bottom side), 12 nets.

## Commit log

2022-09-06 First Version
